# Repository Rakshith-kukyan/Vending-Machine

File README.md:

# Vending-Machine

An IOT based project on Developing UPI enabled Vending Machine using Raspberry Pi Pico W Microcontroller.
       - By Team Byte Burst

![alt text][def]

[def]: ByteBurst.jpg

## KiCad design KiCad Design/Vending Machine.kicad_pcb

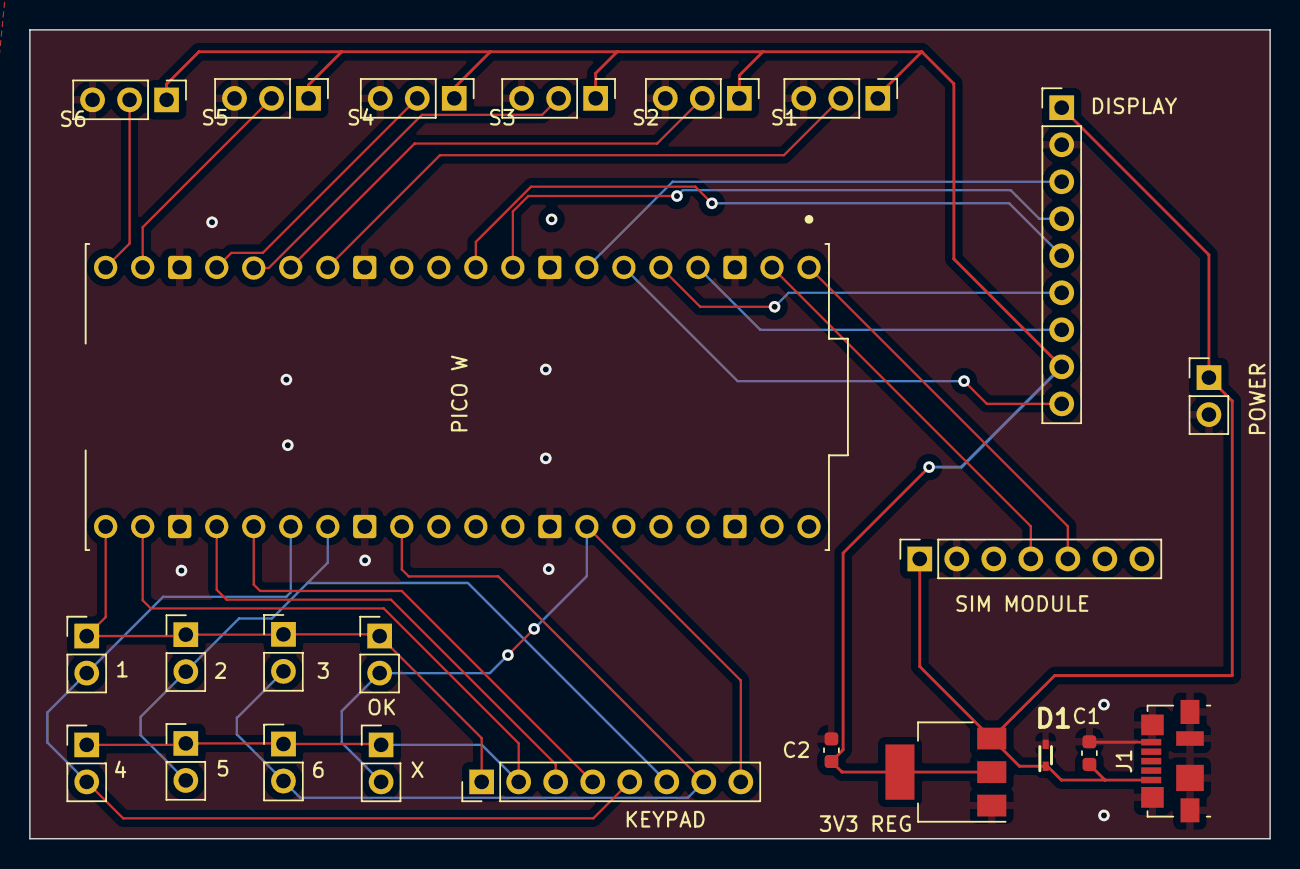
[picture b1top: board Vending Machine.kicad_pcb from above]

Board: 2 copper layers, 85.1 x 55.5 mm, 24 parts (0 on the bottom side), 25 nets.

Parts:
1: 1; PinHeader_1x02_P2.54mm_Vertical
2: 2; PinHeader_1x02_P2.54mm_Vertical
3: 3; PinHeader_1x02_P2.54mm_Vertical
3V3 REG: NCP1117-3.3_SOT223; SOT-223-3_TabPin2
4: 4; PinHeader_1x02_P2.54mm_Vertical
5: 5; PinHeader_1x02_P2.54mm_Vertical
6: 6; PinHeader_1x02_P2.54mm_Vertical
C1, C2: 10u; C_0603_1608Metric
D1: ESD5Z7.0T1G; SODFL1608X70N
DISPLAY: Conn_01x09_Pin; PinHeader_1x09_P2.54mm_Vertical
J1: USB_B_Micro; USB_Micro-B_Molex_47346-0001
KEYPAD: Conn_01x08_Pin; PinHeader_1x08_P2.54mm_Vertical
OK: OK; PinHeader_1x02_P2.54mm_Vertical
PICO W: RASPBERRY_PI_PICO_WH; MODULE_SC0918
POWER: Conn_01x02_Pin; PinHeader_1x02_P2.54mm_Vertical
S1, S2, S3, S4, S5, S6: Conn_01x03_Pin; PinHeader_1x03_P2.54mm_Vertical
SIM MODULE: Conn_01x07_Socket; PinSocket_1x07_P2.54mm_Vertical
X: CANCEL; PinHeader_1x02_P2.54mm_Vertical

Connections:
+3V3: 3V3 REG.2 (VO), C2.1, DISPLAY.8, S1.1, S2.1, S3.1, S4.1, S5.1, S6.1
+5V: 3V3 REG.3 (VI), C1.1, D1.1 (K), DISPLAY.1, J1.1 (VBUS), POWER.1, SIM MODULE.1
/GP2: DISPLAY.7, PICO W.4 (GP2)
/GP3: DISPLAY.6, PICO W.5 (GP3)
/GP4: DISPLAY.9, PICO W.6 (GP4)
/GP5: DISPLAY.3, PICO W.7 (GP5)
/GP6: DISPLAY.4, PICO W.9 (GP6)
/GP7: DISPLAY.5, PICO W.10 (GP7)
/GP10: PICO W.14 (GP10), S1.2
/GP11: PICO W.15 (GP11), S2.2
/GP12: PICO W.16 (GP12), S3.2
/GP13: PICO W.17 (GP13), S4.2
/GP14: PICO W.19 (GP14), S5.2
/GP15: PICO W.20 (GP15), S6.2
/GP16: 1.1, 2.1, 3.1, KEYPAD.1, OK.1, PICO W.21 (GP16)
/GP17: 4.1, 5.1, 6.1, KEYPAD.2, PICO W.22 (GP17), X.1
/GP18: KEYPAD.3, PICO W.24 (GP18)
/GP19: KEYPAD.4, PICO W.25 (GP19)
/GP20: 1.2, 4.2, KEYPAD.5, PICO W.26 (GP20)
/GP21: 2.2, 5.2, KEYPAD.6, PICO W.27 (GP21)
/GP22: 3.2, 6.2, KEYPAD.7, PICO W.29 (GP22)
/GP28: KEYPAD.8, OK.2, PICO W.34 (GP28), X.2
/RX: PICO W.2 (GP1), SIM MODULE.4
/TX: PICO W.1 (GP0), SIM MODULE.5
GND: 3V3 REG.1 (GND), C1.2, C2.2, D1.2 (A), DISPLAY.2, J1.5 (GND), J1.6 (Shield), PICO W.3 (GND_1), PICO W.8 (GND_2), PICO W.13 (GND_3), PICO W.18 (GND_4), PICO W.23 (GND_5), PICO W.28 (GND_6), PICO W.33 (GND_7), PICO W.38 (GND_8), POWER.2, S1.3, S2.3, S3.3, S4.3, S5.3, S6.3, SIM MODULE.2

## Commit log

2024-02-04 Change in resources
2024-02-04 Added pico w datasheet
2024-07-07 Codes Updated
2024-07-27 Update SourceCode
2024-09-17 PCB Design added
